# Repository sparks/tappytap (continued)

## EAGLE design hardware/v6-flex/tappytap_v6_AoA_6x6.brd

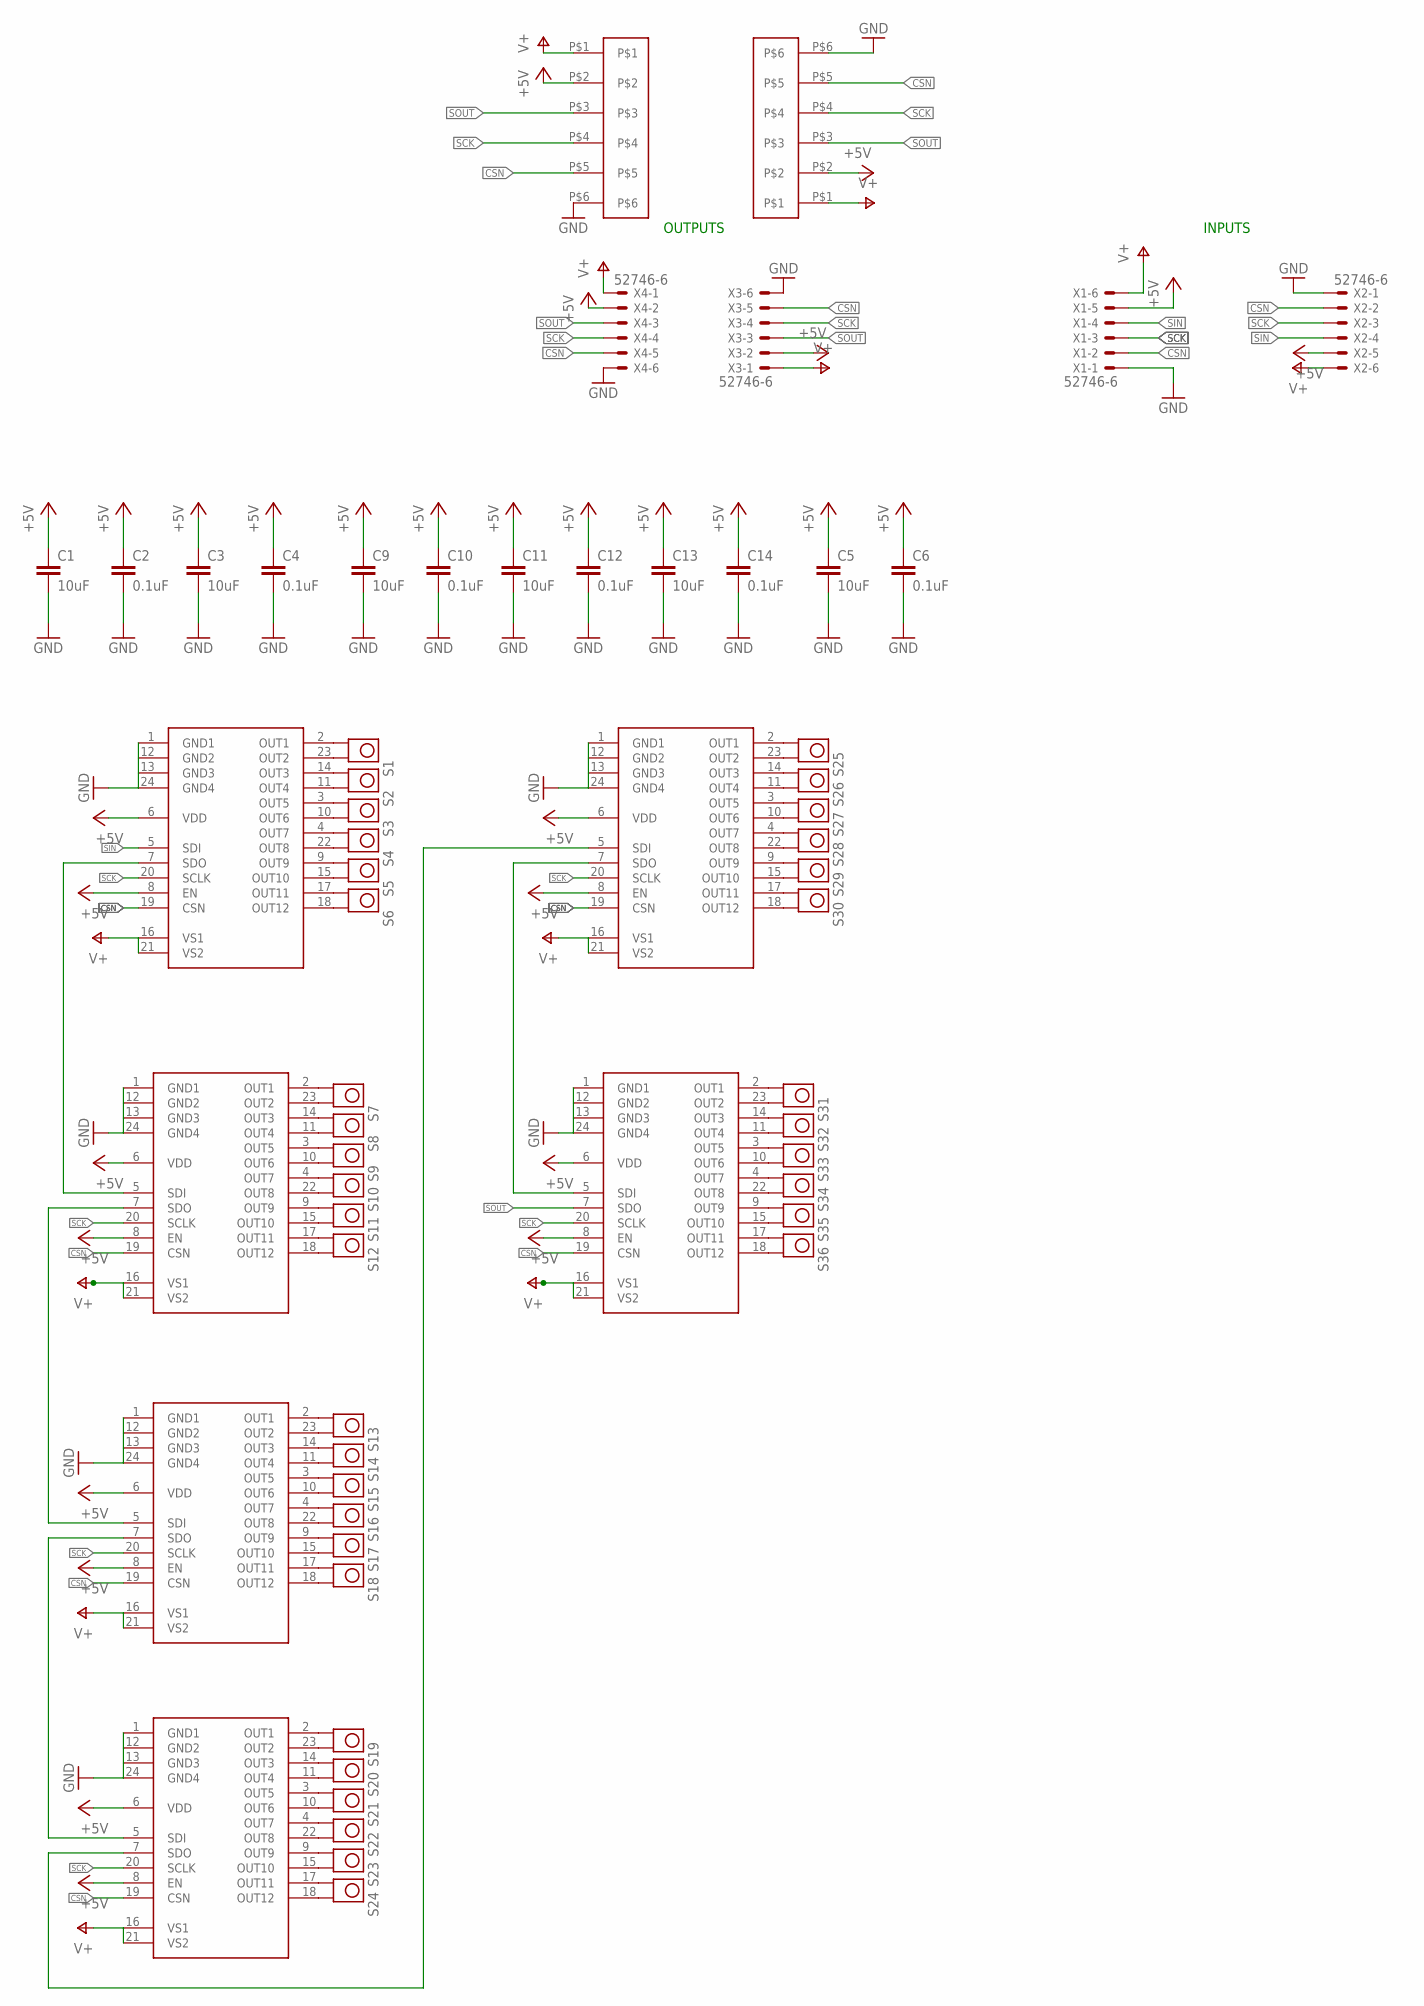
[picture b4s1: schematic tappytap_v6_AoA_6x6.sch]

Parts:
C1, C3, C5, C9, C11, C13: 10uF; C0603
C2, C4, C6, C10, C12, C14: 0.1uF; C0603
S1, S2, S3, S4, S5, S6, S7, S8, S9, S10, S11, S12, S13, S14, S15, S16, S17, S18, S19, S20, S21, S22, S23, S24, S25, S26, S27, S28, S29, S30, S31, S32, S33, S34, S35, S36: TP_4MM_MED_PAD
U$1, U$2, U$3, U$4, U$5, U$6: TLE94112EL_LSSOP24; SSOP-24
U$15, U$16: FLEXTAB_6POS
X1, X2, X3, X4: 52746-6

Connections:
+5V: C1.1, C2.1, C3.1, C4.1, C5.1, C6.1, C9.1, C10.1, C11.1, C12.1, C13.1, C14.1, U$1.6 (VDD), U$1.8 (EN), U$2.6 (VDD), U$2.8 (EN), U$3.6 (VDD), U$3.8 (EN), U$4.6 (VDD), U$4.8 (EN), U$5.6 (VDD), U$5.8 (EN), U$6.6 (VDD), U$6.8 (EN), U$15.P$2, U$16.P$2, X1.5, X2.5, X3.2, X4.2
CSN: U$1.19 (CSN), U$2.19 (CSN), U$3.19 (CSN), U$4.19 (CSN), U$5.19 (CSN), U$6.19 (CSN), U$15.P$5, U$16.P$5, X1.2, X2.2, X3.5, X4.5
GND: C1.2, C2.2, C3.2, C4.2, C5.2, C6.2, C9.2, C10.2, C11.2, C12.2, C13.2, C14.2, U$1.1 (GND1), U$1.12 (GND2), U$1.13 (GND3), U$1.24 (GND4), U$2.1 (GND1), U$2.12 (GND2), U$2.13 (GND3), U$2.24 (GND4), U$3.1 (GND1), U$3.12 (GND2), U$3.13 (GND3), U$3.24 (GND4), U$4.1 (GND1), U$4.12 (GND2), U$4.13 (GND3), U$4.24 (GND4), U$5.1 (GND1), U$5.12 (GND2), U$5.13 (GND3), U$5.24 (GND4), U$6.1 (GND1), U$6.12 (GND2), U$6.13 (GND3), U$6.24 (GND4), U$15.P$6, U$16.P$6, X1.1, X2.1, X3.6, X4.6
unnamed: S19.P$1 (0), U$4.2 (OUT1)
unnamed: U$3.7 (SDO), U$4.5 (SDI)
unnamed: S19.P$2 (1), U$4.23 (OUT2)
unnamed: S20.P$1 (0), U$4.14 (OUT3)
unnamed: S20.P$2 (1), U$4.11 (OUT4)
unnamed: S21.P$1 (0), U$4.3 (OUT5)
unnamed: S1.P$1 (0), U$1.2 (OUT1)
unnamed: S1.P$2 (1), U$1.23 (OUT2)
unnamed: S2.P$1 (0), U$1.14 (OUT3)
unnamed: S2.P$2 (1), U$1.11 (OUT4)
unnamed: S3.P$1 (0), U$1.3 (OUT5)
unnamed: S3.P$2 (1), U$1.10 (OUT6)
unnamed: S4.P$1 (0), U$1.4 (OUT7)
unnamed: S4.P$2 (1), U$1.22 (OUT8)
unnamed: S5.P$1 (0), U$1.9 (OUT9)
unnamed: S5.P$2 (1), U$1.15 (OUT10)
unnamed: S6.P$1 (0), U$1.17 (OUT11)
unnamed: S6.P$2 (1), U$1.18 (OUT12)
unnamed: S7.P$1 (0), U$2.2 (OUT1)
unnamed: S7.P$2 (1), U$2.23 (OUT2)
unnamed: S8.P$1 (0), U$2.14 (OUT3)
unnamed: S8.P$2 (1), U$2.11 (OUT4)
unnamed: S9.P$1 (0), U$2.3 (OUT5)
unnamed: S21.P$2 (1), U$4.10 (OUT6)
unnamed: S9.P$2 (1), U$2.10 (OUT6)
unnamed: S22.P$1 (0), U$4.4 (OUT7)
unnamed: S10.P$1 (0), U$2.4 (OUT7)
unnamed: S10.P$2 (1), U$2.22 (OUT8)
unnamed: S11.P$1 (0), U$2.9 (OUT9)
unnamed: S11.P$2 (1), U$2.15 (OUT10)
unnamed: S12.P$1 (0), U$2.17 (OUT11)
unnamed: S12.P$2 (1), U$2.18 (OUT12)
unnamed: S13.P$1 (0), U$3.2 (OUT1)
unnamed: S13.P$2 (1), U$3.23 (OUT2)
unnamed: S14.P$1 (0), U$3.14 (OUT3)
unnamed: S14.P$2 (1), U$3.11 (OUT4)
unnamed: S15.P$1 (0), U$3.3 (OUT5)
unnamed: S15.P$2 (1), U$3.10 (OUT6)
unnamed: S16.P$1 (0), U$3.4 (OUT7)
unnamed: S16.P$2 (1), U$3.22 (OUT8)
unnamed: S17.P$1 (0), U$3.9 (OUT9)
unnamed: S17.P$2 (1), U$3.15 (OUT10)
unnamed: S18.P$1 (0), U$3.17 (OUT11)
unnamed: S18.P$2 (1), U$3.18 (OUT12)
unnamed: U$2.7 (SDO), U$3.5 (SDI)
unnamed: U$1.7 (SDO), U$2.5 (SDI)
unnamed: S22.P$2 (1), U$4.22 (OUT8)
unnamed: S23.P$1 (0), U$4.9 (OUT9)
unnamed: S23.P$2 (1), U$4.15 (OUT10)
unnamed: S24.P$1 (0), U$4.17 (OUT11)
unnamed: S24.P$2 (1), U$4.18 (OUT12)
unnamed: U$4.7 (SDO), U$5.5 (SDI)
unnamed: S25.P$1 (0), U$5.2 (OUT1)
unnamed: S25.P$2 (1), U$5.23 (OUT2)
unnamed: S26.P$1 (0), U$5.14 (OUT3)
unnamed: S26.P$2 (1), U$5.11 (OUT4)
unnamed: S27.P$1 (0), U$5.3 (OUT5)
unnamed: S27.P$2 (1), U$5.10 (OUT6)
unnamed: S28.P$1 (0), U$5.4 (OUT7)
unnamed: S28.P$2 (1), U$5.22 (OUT8)
unnamed: S29.P$1 (0), U$5.9 (OUT9)
unnamed: S29.P$2 (1), U$5.15 (OUT10)
unnamed: S30.P$1 (0), U$5.17 (OUT11)
unnamed: S30.P$2 (1), U$5.18 (OUT12)
unnamed: S31.P$1 (0), U$6.2 (OUT1)
unnamed: S31.P$2 (1), U$6.23 (OUT2)
unnamed: S32.P$1 (0), U$6.14 (OUT3)
unnamed: S32.P$2 (1), U$6.11 (OUT4)
unnamed: S33.P$1 (0), U$6.3 (OUT5)
unnamed: S33.P$2 (1), U$6.10 (OUT6)
unnamed: S34.P$1 (0), U$6.4 (OUT7)
unnamed: S34.P$2 (1), U$6.22 (OUT8)
unnamed: S35.P$1 (0), U$6.9 (OUT9)
unnamed: S35.P$2 (1), U$6.15 (OUT10)
unnamed: S36.P$1 (0), U$6.17 (OUT11)
unnamed: S36.P$2 (1), U$6.18 (OUT12)
unnamed: U$5.7 (SDO), U$6.5 (SDI)
SCK: U$1.20 (SCLK), U$2.20 (SCLK), U$3.20 (SCLK), U$4.20 (SCLK), U$5.20 (SCLK), U$6.20 (SCLK), U$15.P$4, U$16.P$4, X1.3, X2.3, X3.4, X4.4
SIN: U$1.5 (SDI), X1.4, X2.4
SOUT: U$6.7 (SDO), U$15.P$3, U$16.P$3, X3.3, X4.3
V+: U$1.16 (VS1), U$1.21 (VS2), U$2.16 (VS1), U$2.21 (VS2), U$3.16 (VS1), U$3.21 (VS2), U$4.16 (VS1), U$4.21 (VS2), U$5.16 (VS1), U$5.21 (VS2), U$6.16 (VS1), U$6.21 (VS2), U$15.P$1, U$16.P$1, X1.6, X2.6, X3.1, X4.1

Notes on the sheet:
OUTPUTS
INPUTS

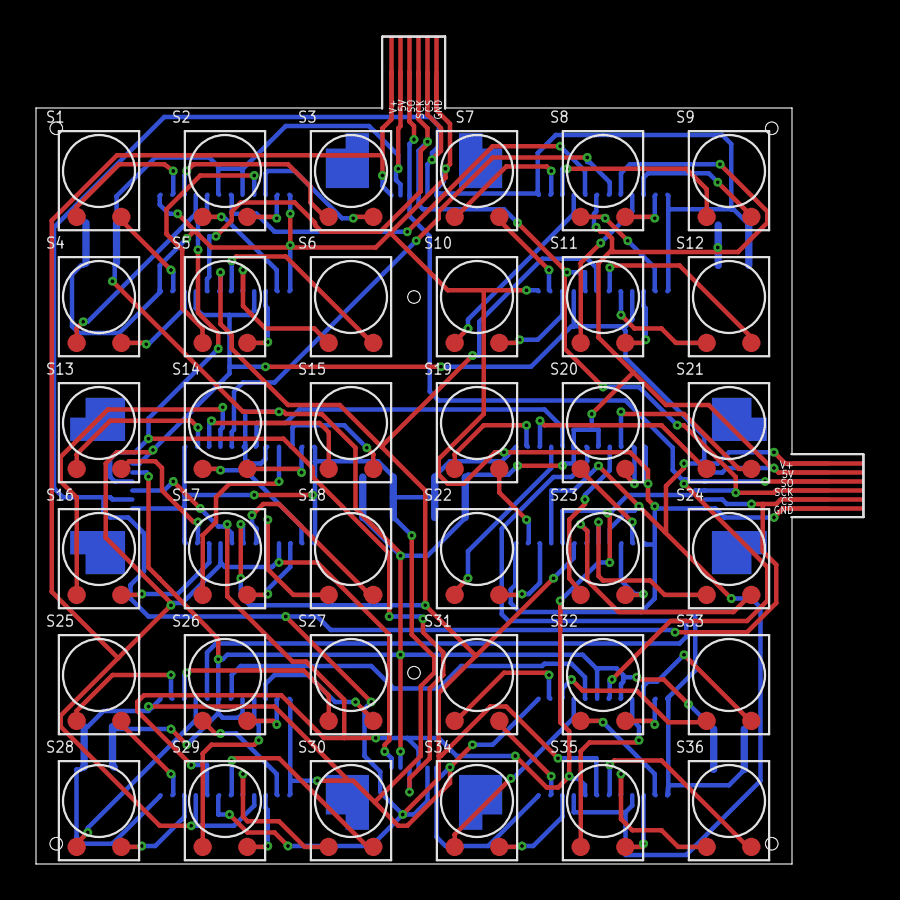
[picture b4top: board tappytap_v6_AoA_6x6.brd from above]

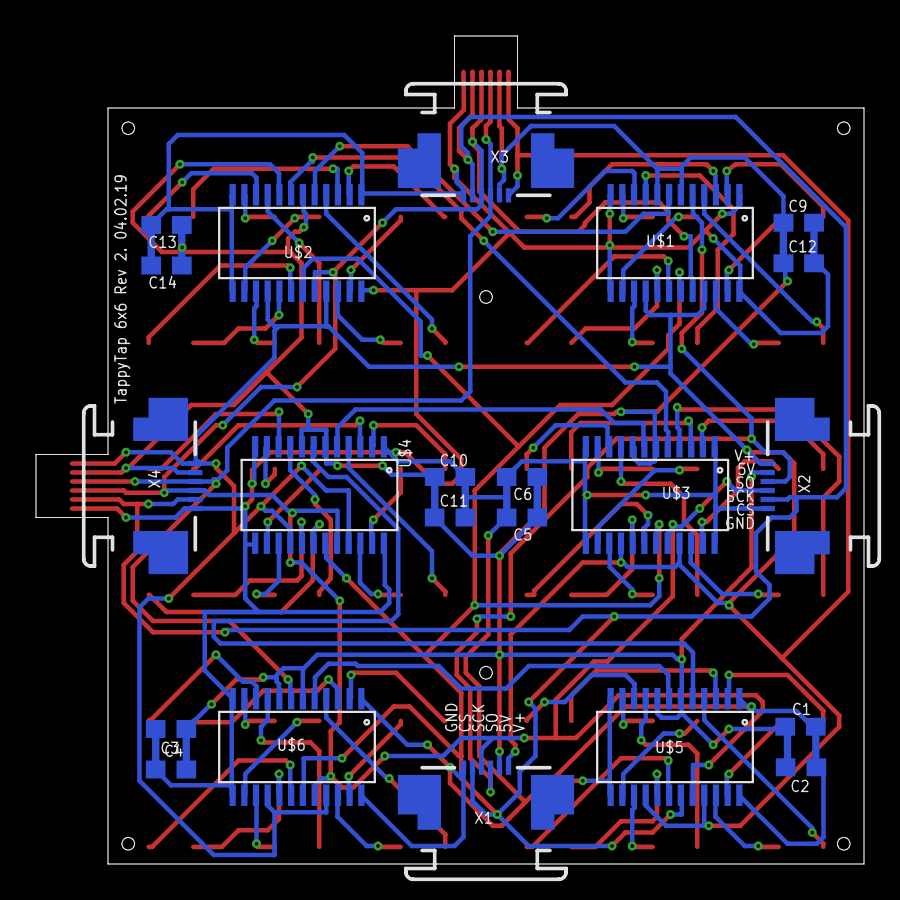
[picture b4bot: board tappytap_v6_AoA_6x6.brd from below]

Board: 2 copper layers, 46.0 x 46.0 mm, 60 parts (22 on the bottom side), 84 nets.
